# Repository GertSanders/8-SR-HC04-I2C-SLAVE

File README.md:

# 8-SR-HC04-I2C-SLAVE
An I2C slave with connectors for 8 SR-HC04's, will ping all sensors and provide an array of distances.

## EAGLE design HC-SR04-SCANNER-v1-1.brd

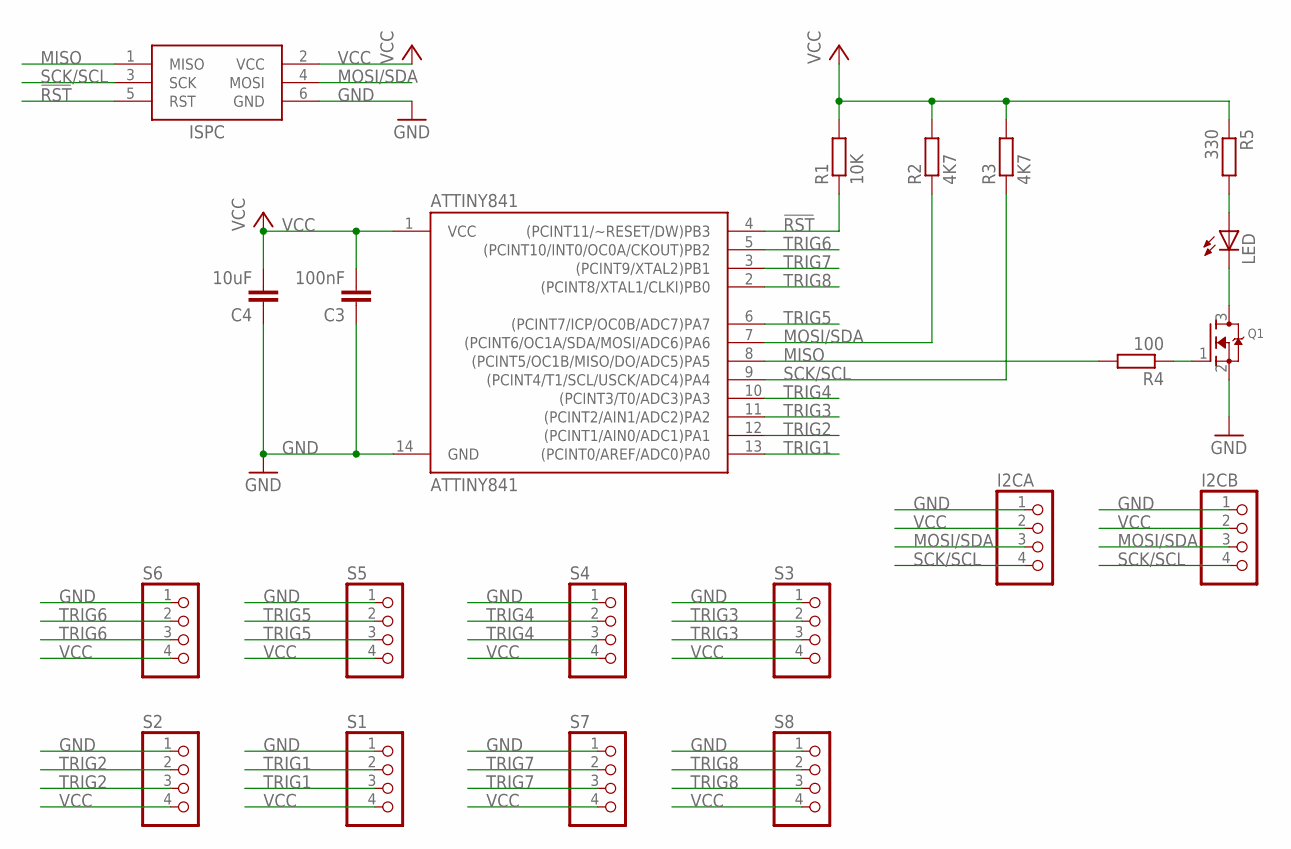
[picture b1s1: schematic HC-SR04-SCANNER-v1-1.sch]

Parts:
ATTINY841: ATTINY841; SO14
C3: 100nF; C0805K
C4: 10uF; C0805K
I2CA, I2CB: PINHD-1X4; 1X04
ISPC: AVRISP-6; AVRISP
LED: LED; LED_0805
Q1: MOSFET-NREFLOW; SOT23
R1: 10K; R0805
R2, R3: 4K7; R0805
R4: 100; R0805
R5: 330; R0805
S1, S2, S3, S4, S5, S6, S7, S8: PINHD-1X4; 1X04

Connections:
!RST: ATTINY841.4 ((PCINT11/~RESET/DW)PB3), ISPC.5 (RST), R1.1
GND: ATTINY841.14 (GND), C3.1, C4.1, I2CA.1, I2CB.1, ISPC.6 (GND), Q1.2 (S), S1.1, S2.1, S3.1, S4.1, S5.1, S6.1, S7.1, S8.1
MISO: ATTINY841.8 ((PCINT5/OC1B/MISO/DO/ADC5)PA5), ISPC.1 (MISO), R4.2
MOSI/SDA: ATTINY841.7 ((PCINT6/OC1A/SDA/MOSI/ADC6)PA6), I2CA.3, I2CB.3, ISPC.4 (MOSI), R2.1
unnamed: Q1.1 (G), R4.1
unnamed: LED.1 (A), R5.2
unnamed: LED.2 (C), Q1.3 (D)
SCK/SCL: ATTINY841.9 ((PCINT4/T1/SCL/USCK/ADC4)PA4), I2CA.4, I2CB.4, ISPC.3 (SCK), R3.1
TRIG1: ATTINY841.13 ((PCINT0/AREF/ADC0)PA0), S1.2, S1.3
TRIG2: ATTINY841.12 ((PCINT1/AIN0/ADC1)PA1), S2.2, S2.3
TRIG3: ATTINY841.11 ((PCINT2/AIN1/ADC2)PA2), S3.2, S3.3
TRIG4: ATTINY841.10 ((PCINT3/T0/ADC3)PA3), S4.2, S4.3
TRIG5: ATTINY841.6 ((PCINT7/ICP/OC0B/ADC7)PA7), S5.2, S5.3
TRIG6: ATTINY841.5 ((PCINT10/INT0/OC0A/CKOUT)PB2), S6.2, S6.3
TRIG7: ATTINY841.3 ((PCINT9/XTAL2)PB1), S7.2, S7.3
TRIG8: ATTINY841.2 ((PCINT8/XTAL1/CLKI)PB0), S8.2, S8.3
VCC: ATTINY841.1 (VCC), C3.2, C4.2, I2CA.2, I2CB.2, ISPC.2 (VCC), R1.2, R2.2, R3.2, R5.1, S1.4, S2.4, S3.4, S4.4, S5.4, S6.4, S7.4, S8.4

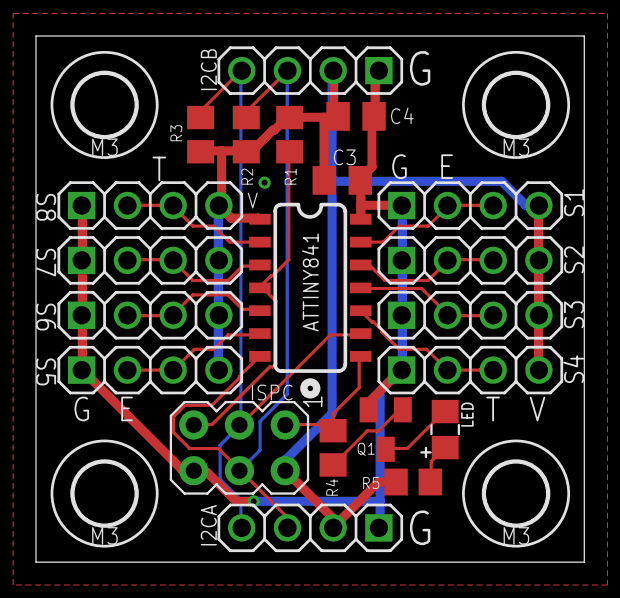
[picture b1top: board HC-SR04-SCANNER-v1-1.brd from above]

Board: 2 copper layers, 30.5 x 29.2 mm, 26 parts (1 on the bottom side), 17 nets.

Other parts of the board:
U$1: OSHWLOGO_TOL_0.2
U$2, U$3, U$4, U$5: HOLE_M3PAN_LOOSE

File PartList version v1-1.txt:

Partlist

Exported from HC-SR04-SCANNER-v1-1.sch at 08/04/2018 23:13

EAGLE Version 8.7.1 Copyright (c) 1988-2018 Autodesk, Inc.

Assembly variant: 

Part      Value          Device         Package  Library      Sheet

ATTINY841 ATTINY841      ATTINY84       SO14     miller       1
C3        100nF          C-EUC0805K     C0805K   GertSanders  1
C4        10uF           C-EUC0805K     C0805K   GertSanders  1
I2CA                     PINHD-1X4      1X04     GertSanders  1
I2CB                     PINHD-1X4      1X04     GertSanders  1
ISPC      AVRISP-6       AVRISP-6       AVRISP   adafruit     1
LED       BLUE           LED            LED_0805 TD-MySensors 1
Q1        2N7002         MOSFET-NREFLOW SOT23    GertSanders  1
R1        10K            R-EU_R0805     R0805    rcl          1
R2        4K7            R-EU_R0805     R0805    rcl          1
R3        4K7            R-EU_R0805     R0805    rcl          1
R4        100            R-EU_R0805     R0805    rcl          1
R5        330            R-EU_R0805     R0805    rcl          1
S1                       PINHD-1X4      1X04     GertSanders  1
S2                       PINHD-1X4      1X04     GertSanders  1
S3                       PINHD-1X4      1X04     GertSanders  1
S4                       PINHD-1X4      1X04     GertSanders  1
S5                       PINHD-1X4      1X04     GertSanders  1
S6                       PINHD-1X4      1X04     GertSanders  1
S7                       PINHD-1X4      1X04     GertSanders  1
S8                       PINHD-1X4      1X04     GertSanders  1

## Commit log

2018-04-08 Added version 1 board file and schematic
2018-04-08 Added board file and schematic for versions v1-1 (untested).
2018-04-08 Added part list for version v1-1
2018-04-08 Added the sketch for the I2C slave
    Code to use in the I2C Master is added in the comments.
